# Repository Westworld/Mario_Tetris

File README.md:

# Mix of Mario Bros. and Tetris Clock

Using 64x64 DMD matrix as clock to run
Marios Bros, Tetris and Blockout

This is a clone based on:
https://github.com/jnthas/mariobros-clock/b

and

https://github.com/toblum/TetrisAnimation

## Modification made for Mario:

- removed Wifi Connection assistant and replaced with hard coded credentials using WifiMulti. Benefit: allows to enter network access credentials for 2 networks, makes moving the clock from office/home (etc) easy. And allows to handle daylight saving time update
- rewrote to virtual matrix display, allows usage of two 64x32 panels instead of one 64x64 panel
- overwrote standard pins to allow different, much more easy, routing from ESP32 to HUB75.

## Modification for Tetris
- just using library

# Game
Clock starts switches every 10 minutes between Tetris and Mario Bors. and Blockout

## PCB 
A simple board to hold ESP32 and HUB75 was created with Eagle. Mil files to use a CNC to create your own PCB is enclosed.

## Case
Instead of a case a holder (to mount 2 panels) with a stand is enclosed.

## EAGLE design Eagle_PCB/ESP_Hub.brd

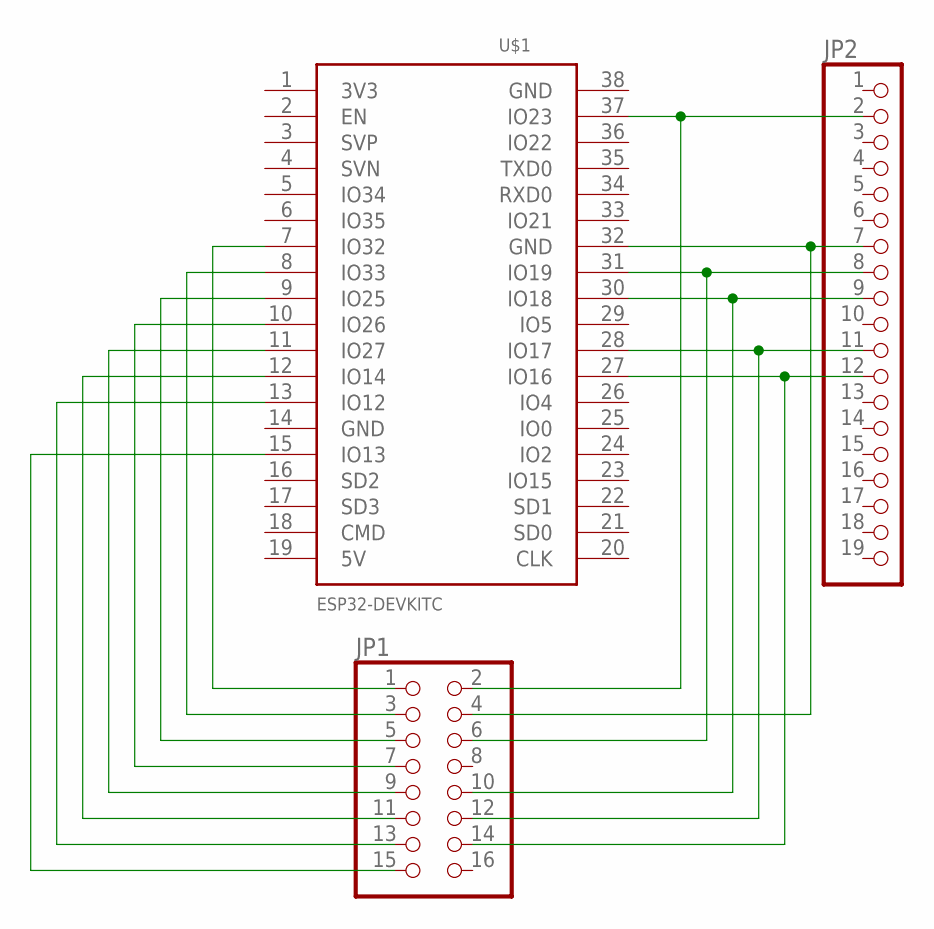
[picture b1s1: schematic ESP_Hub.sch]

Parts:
JP1: PINHD-2X8; 2X08
JP2: PINHD-1X19; 1X19
U$1: ESP32DEVKITC; ESP32-DEVKITC

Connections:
unnamed: JP1.1, U$1.7 (IO32)
unnamed: JP1.3, U$1.8 (IO33)
unnamed: JP1.5, U$1.9 (IO25)
unnamed: JP1.15, U$1.15 (IO13)
unnamed: JP1.7, U$1.10 (IO26)
unnamed: JP1.9, U$1.11 (IO27)
unnamed: JP1.11, U$1.12 (IO14)
unnamed: JP1.13, U$1.13 (IO12)
unnamed: JP1.2, JP2.2, U$1.37 (IO23)
unnamed: JP1.6, JP2.8, U$1.31 (IO19)
unnamed: JP1.10, JP2.9, U$1.30 (IO18)
unnamed: JP1.12, JP2.11, U$1.28 (IO17)
unnamed: JP1.14, JP2.12, U$1.27 (IO16)
unnamed: JP1.4, JP2.7, U$1.32 (GND)

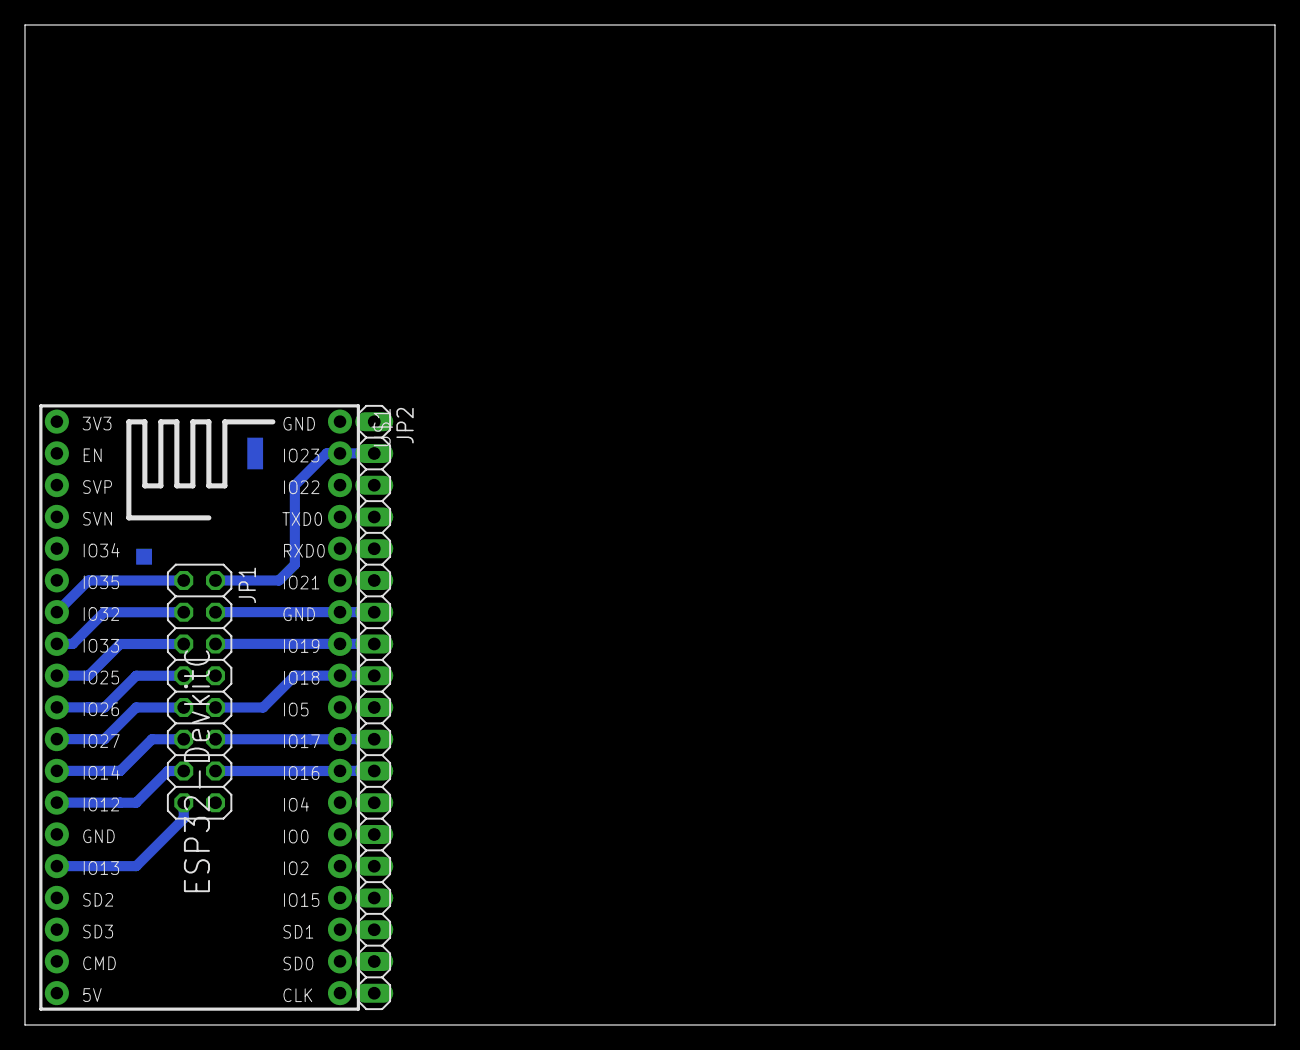
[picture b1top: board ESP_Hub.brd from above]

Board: 2 copper layers, 100.0 x 80.0 mm, 3 parts (0 on the bottom side), 14 nets.

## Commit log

2022-06-29 first commit, Mario working
2022-06-29 adding Eagle
2022-07-03 Mario + Tetris working
2022-07-08 added Blockout as 3rd Game
2022-07-16 last update, before starting display optimization
